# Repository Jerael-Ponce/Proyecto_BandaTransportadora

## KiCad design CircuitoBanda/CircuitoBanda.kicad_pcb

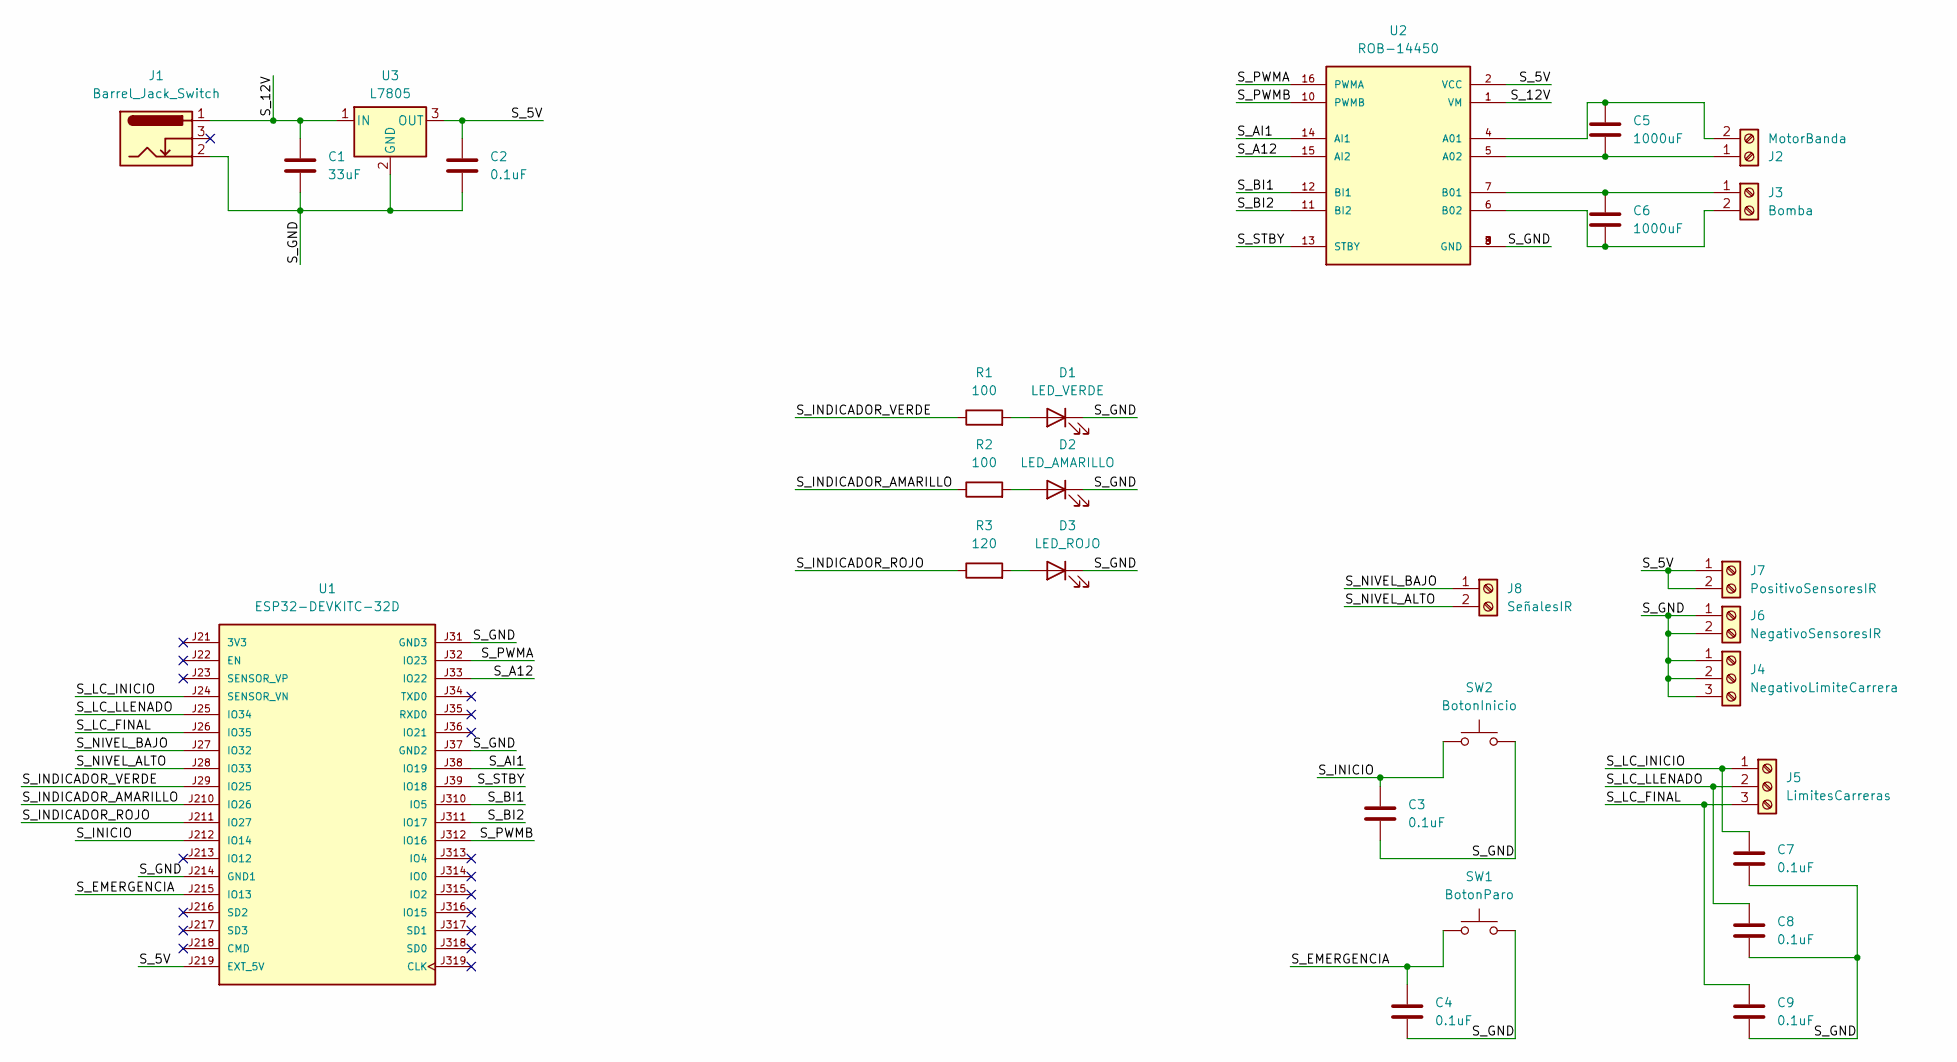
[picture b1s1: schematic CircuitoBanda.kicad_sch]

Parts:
C1: 33uF; C_Disc_D5.0mm_W2.5mm_P2.50mm
C2, C3, C4, C7, C8, C9: 0.1uF; C_Disc_D5.0mm_W2.5mm_P2.50mm
C5, C6: 1000uF; C_Radial_D12.5mm_H20.0mm_P5.00mm
D1: LED_VERDE; LED_D3.0mm_Clear
D2: LED_AMARILLO; LED_D3.0mm_FlatTop
D3: LED_ROJO; LED_D3.0mm
J1: Barrel_Jack_Switch; BarrelJack_Horizontal
J2: MotorBanda; TerminalBlock_Phoenix_MKDS-1,5-2-5.08_1x02_P5.08mm_Horizont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
J3: Bomba; TerminalBlock_Phoenix_MKDS-1,5-2-5.08_1x02_P5.08mm_Horizont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
J4: NegativoLimiteCarrera; TerminalBlock_Phoenix_MKDS-1,5-3-5.08_1x03_P5.08mm_Horizont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
J5: LimitesCarreras; TerminalBlock_Phoenix_MKDS-1,5-3-5.08_1x03_P5.08mm_Horizont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
J6: NegativoSensoresIR; TerminalBlock_Phoenix_MKDS-1,5-2-5.08_1x02_P5.08mm_Horizont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
J7: PositivoSensoresIR; TerminalBlock_Phoenix_MKDS-1,5-2-5.08_1x02_P5.08mm_Horizont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
J8: SeñalesIR; TerminalBlock_Phoenix_MKDS-1,5-2-5.08_1x02_P5.08mm_Horizont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
R1, R2: 100; R_Axial_DIN0204_L3.6mm_D1.6mm_P5.08mm_Horizontal
R3: 120; R_Axial_DIN0204_L3.6mm_D1.6mm_P5.08mm_Horizontal
SW1: BotonParo; SW_PUSH_1P1T_6x3.5mm_H4.3_APEM_MJTP1243
SW2: BotonInicio; SW_PUSH_1P1T_6x3.5mm_H4.3_APEM_MJTP1243
U1: ESP32-DEVKITC-32D; MODULE_ESP32-DEVKITC-32D; PARTREV V4
U2: ROB-14450; MODULE_ROB-14450; PARTREV 11-13-17
U3: L7805; TO-220-3_Vertical

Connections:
/S_5V: C2.1, J7.1, J7.2, U1.J219 (EXT_5V), U2.2 (VCC), U3.3 (OUT)
/S_12V: C1.1, J1.1, U2.1 (VM), U3.1 (IN)
/S_A12: U1.J33 (IO22), U2.15 (AI2)
/S_AI1: U1.J38 (IO19), U2.14 (AI1)
/S_BI1: U1.J310 (IO5), U2.12 (BI1)
/S_BI2: U1.J311 (IO17), U2.11 (BI2)
/S_EMERGENCIA: C4.1, SW1.1, U1.J215 (IO13)
/S_GND: C1.2, C2.2, C3.2, C4.2, C7.2, C8.2, C9.2, D1.1 (K), D2.1 (K), D3.1 (K), J1.2, J4.1, J4.2, J4.3, J6.1, J6.2, SW1.2, SW2.2, U1.J31 (GND3), U1.J37 (GND2), U1.J214 (GND1), U2.3 (GND), U2.8 (GND), U2.9 (GND), U3.2 (GND)
/S_INDICADOR_AMARILLO: R2.1, U1.J210 (IO26)
/S_INDICADOR_ROJO: R3.1, U1.J211 (IO27)
/S_INDICADOR_VERDE: R1.1, U1.J29 (IO25)
/S_INICIO: C3.1, SW2.1, U1.J212 (IO14)
/S_LC_FINAL: C9.1, J5.3, U1.J26 (IO35)
/S_LC_INICIO: C7.1, J5.1, U1.J24 (SENSOR_VN)
/S_LC_LLENADO: C8.1, J5.2, U1.J25 (IO34)
/S_NIVEL_ALTO: J8.2, U1.J28 (IO33)
/S_NIVEL_BAJO: J8.1, U1.J27 (IO32)
/S_PWMA: U1.J32 (IO23), U2.16 (PWMA)
/S_PWMB: U1.J312 (IO16), U2.10 (PWMB)
/S_STBY: U1.J39 (IO18), U2.13 (STBY)
unnamed: D1.2 (A), R1.2
unnamed: D2.2 (A), R2.2
unnamed: D3.2 (A), R3.2
unnamed: C5.2, J2.1, U2.5 (A02)
unnamed: C5.1, J2.2, U2.4 (A01)
unnamed: C6.1, J3.1, U2.7 (B01)
unnamed: C6.2, J3.2, U2.6 (B02)

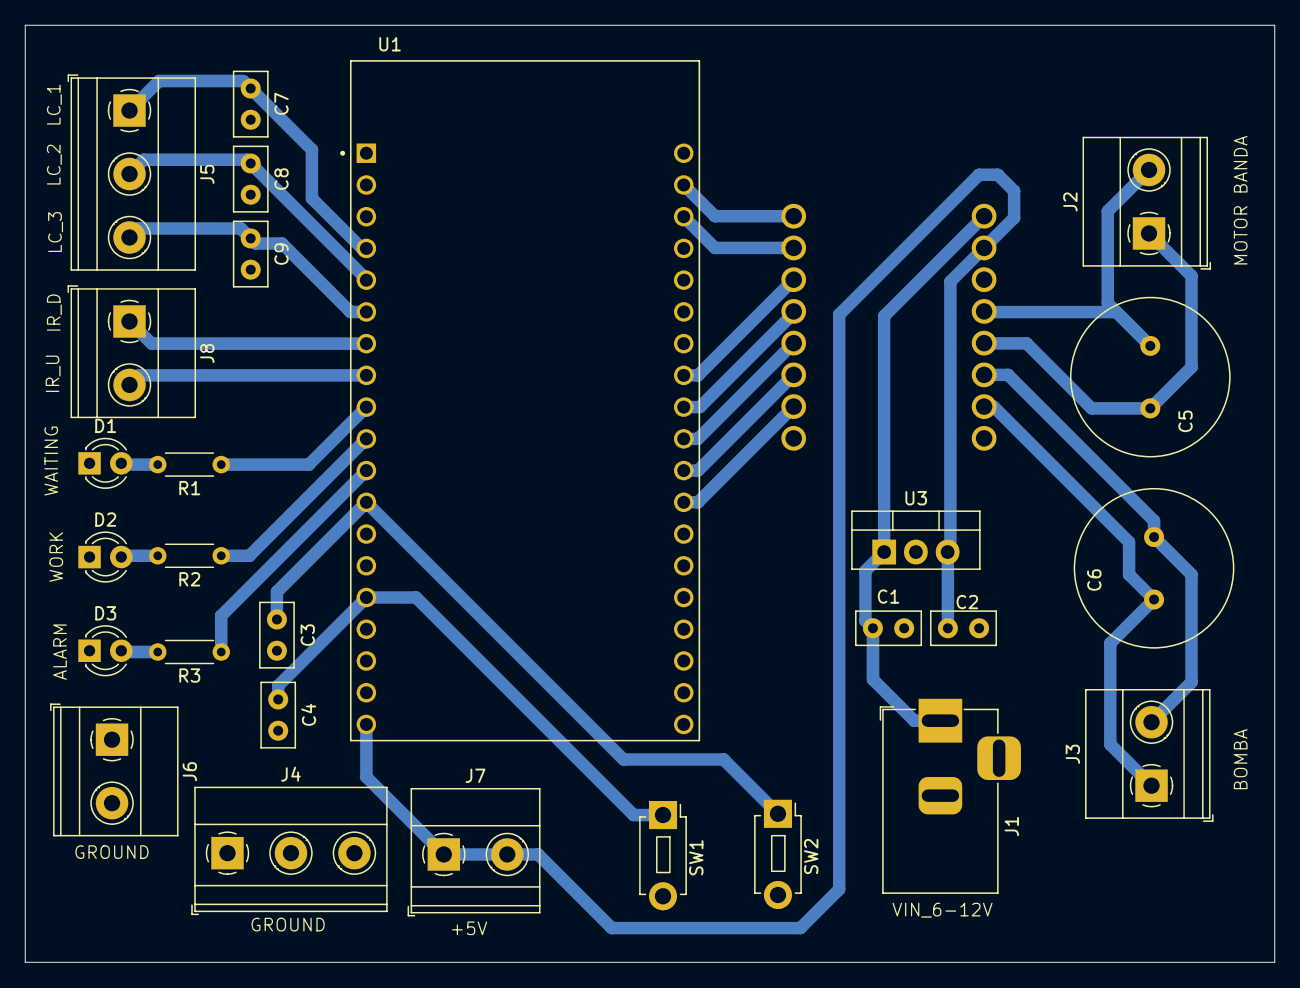
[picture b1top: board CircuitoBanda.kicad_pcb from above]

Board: 2 copper layers, 100.0 x 75.0 mm, 28 parts (1 on the bottom side), 27 nets.

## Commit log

2025-04-09 archivos para compartir
2025-04-09 Sistema Electronico
2025-04-09 SistemaMecanico
